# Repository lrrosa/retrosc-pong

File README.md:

# RetroSC Pong — Raspberry Pi Pico (RP2040)

Pong para 1 ou 2 jogadores em um Raspberry Pi Pico, com saída de **vídeo
composto** (NTSC 1-bit gerado por PIO) e **áudio PWM**. Foi feito para uma
máquina arcade do evento [**RetroSC**](https://retrosc.org/).

## Recursos

- Vídeo composto NTSC 256×192, 1-bit, ~60 Hz, gerado inteiramente em PIO + DMA
  (CPU livre para o jogo).
- 2 raquetes controladas por **potenciômetros 10 kΩ** (ADC do Pico).
- **Dois modos**, escolhidos no menu do attract: **arcade** (1 jogador contra a
  CPU) e **versus** (2 jogadores). Os dois jogam as mesmas fases.
- **11 fases** em sequência, em ordem crescente de dificuldade, cada uma até
  9 pontos, e cada ponto soma no **total geral**:
  1. **PONG CLASSICO** — o pong de sempre;
  2. **TRIPLO** — a raquete vira 3 pedaços de 8 px com vãos entre eles;
  3. **NAVE** — uma nave sobe e desce no meio da quadra atirando: **a bola
     rebate nela** e o tiro que pega uma raquete deixa ela pela metade por 5 s.
     Quem acerta a nave leva o troco: ela revida na hora, com um tiro pelo lado
     de quem rebateu a bola;
  4. **PEBOLIM** — cada jogador tem **três barras**, uma atrás da outra, todas
     no mesmo pot: a de trás (o goleiro, do tamanho da raquete inteira), a do
     meio e a da frente (a menor). As duas das pontas andam juntas e **a do
     meio anda ao contrário** — subir o pot desce a barra do meio. Com o pot no
     meio do curso as três se alinham, que é a posição mais fraca: quem quer
     duas linhas de defesa tem que sair do centro;
  5. **BARREIRA I** — 2 muros de tijolos quebráveis no meio da tela;
  6. **PINBALL** — sete obstáculos fixos no meio da quadra: um losango com um
     poste solto acima e outro abaixo;
  7. **BARREIRA II** — 3 muros, agora espaçados entre si;
  8. **COLUNA** — cinco dos mesmos obstáculos, empilhados no meio e subindo e
     descendo juntos;
  9. **MURALHA** — uma parede de tijolos atrás de cada raquete, com poucos vãos
     abertos de saída: só marca ponto quem enfia a bola num deles. Cada bola que
     passa da raquete derruba mais um tijolo e **o estrago fica até o fim da
     fase**, então a parede vai se abrindo e a fase acelerando;
  10. **REBOUND** — vôlei: as raquetes deitam no chão e andam na horizontal
      dentro da própria meia-quadra, a bola tem gravidade e o ponto sai quando
      ela toca o chão do lado adversário;
  11. **BARREIRA III** — 4 muros (2 por jogador), já divididos em blocos de
      5-4-2-4-5 fileiras com um corredor vazio entre eles: a mais dura, por
      isso fecha o jogo.

  Nas três barreiras o estrago fica até o fim da fase: quando abre um vão de
  ponta a ponta, aquela fase volta a ser um pong normal.
- **Mascote-bônus**: em quatro fases — **1 (clássico), 2 (triplo), 4 (barreira I)
  e 8 (muralha)**, as que têm o meio da quadra livre — o
  mascote da RetroSC cruza a tela na diagonal — às vezes de cima para baixo,
  às vezes de baixo para cima — com a palavra **BONUS** piscando ao lado. Ele
  passa **no máximo duas vezes por fase**, e acertá-lo com a bola dá um prêmio
  **sorteado na hora** para quem rebateu por último — o nome dele aparece por
  2 s do lado de quem levou. A CPU joga com as mesmas armas:

  | prêmio | o que faz |
  | --- | --- |
  | **BONUS +3** | 3 pontos **só no total geral** — o placar da fase não muda, e o total pisca um instante |
  | **RAQUETE MAIOR** | a sua raquete cresce 50% por 10 s |
  | **ENCOLHEU O RIVAL** | a raquete do adversário fica pela metade por 10 s |
  | **ESCUDO** | um muro de tijolos quebráveis aparece na frente do seu gol por 10 s; ele tem vãos por onde a bola ainda passa, some tijolo a tijolo e pisca no último segundo |
  | **TURBO** | por 10 s, cada bola que **você** rebate sai acelerada; ela volta ao normal sozinha depois de 1,5 s e só acelera de novo no seu próximo toque |

  Os quatro efeitos temporizados contam 10 s de **jogo** e atravessam o ponto:
  quem ganha no fim de um rali leva o resto do tempo para o seguinte.
  O mascote anda devagar de propósito — ele é alvo, não obstáculo. Quem limita
  a chance de acertá-lo é a duração do ponto, porque **todo ponto marcado o tira
  da tela**; por isso ele fica ~4,6 s em cena e é acertado em 1 de cada 4
  passagens.
- **Pausa**: apertar o SELETOR durante a partida abre *CONTINUAR* / *SAIR DO
  JOGO*. A escolha anda pelo **movimento** do pot (não pela posição dele), então
  o menu sempre abre em *CONTINUAR*; o SELETOR confirma e sair volta ao attract.
  Passados **30 s**, a opção destacada vale sozinha — a tela não fica parada
  para sempre numa máquina de evento.
  Ao voltar ao jogo, a raquete de quem mexeu no pot durante a pausa fica
  **piscando e parada** até o pot voltar ao lugar em que estava — pausar não
  serve para reposicionar a raquete e salvar uma bola perdida.
- **Attract screen** com logo da RetroSC + demo automático (AI vs AI),
  revezando com a tabela de recordes a cada 20 s, e um **menu de modo** que só
  aparece depois de apertar o botão **SELETOR**.
- **High scores persistentes** na flash do RP2040 com **iniciais de 3 letras**
  estilo arcade — o pot escolhe cada letra e o botão SELETOR confirma. O que
  entra no ranking é o **total acumulado** (no arcade, sempre o do humano —
  ou seja, quanto ele fez até a fase em que parou).
- Áudio com os sons clássicos do Pong (raquete, parede, ponto) mais tijolo
  quebrado e beeps do menu, em PWM filtrado.
- Botão **SELETOR**: abre o menu, escolhe o modo e confirma as iniciais.

## Estrutura do repositório

```
pong-rp2040/
├── CMakeLists.txt
├── pico_sdk_import.cmake
├── README.md
├── LICENSE
├── docs/
│   ├── schematic.md     <-- esquemático por blocos (diagramas SVG)
│   ├── pinout.md        <-- pinagem dos 3 módulos RP2040 suportados
│   ├── bom.md           <-- lista de materiais (por referência: R1, C2, J4…)
│   ├── pecas-do-gabinete.md  <-- pots, knobs e itens da caixa: qual comprar
│   └── images/          <-- diagramas, renders da placa, capturas
├── kicad/               <-- PCB: 2 variantes, gerbers prontos p/ fábrica
│   ├── README.md        <-- pipeline (esquemático -> placa -> gerbers)
│   ├── retrosc-pong*.kicad_{sch,pcb,pro}
│   ├── retrosc-pong.pretty/   <-- footprints próprios (RCA, PAM8403)
│   └── gerbers*/ + *-gerbers.zip
├── src/
│   ├── main.c
│   ├── config.h         <-- constantes do projeto (pinos, dimensões, etc.)
│   ├── ntsc.{c,h,pio}   <-- driver de vídeo composto
│   ├── gfx.{c,h}        <-- desenho no framebuffer
│   ├── font.{c,h}       <-- fonte 5x7
│   ├── input.{c,h}      <-- ADC dos pots + botão
│   ├── audio.{c,h}      <-- PWM de áudio
│   ├── highscores.{c,h} <-- persistência na flash
│   ├── game.{c,h}       <-- máquina de estados, modos e física
│   ├── phases.{c,h}     <-- as 4 fases (raquetes especiais, tijolos)
│   └── assets.{c,h}     <-- bitmaps embutidos
└── tools/
    ├── png_to_c.py      <-- conversor PNG → C array
    ├── sim.py           <-- simulador do jogo (pygame)
    ├── crt_preview.py   <-- efeito de tubo nas capturas
    ├── gen_kicad_sch.py <-- gera o esquemático  (--yd p/ a variante)
    ├── gen_kicad_fp.py  <-- gera os footprints próprios
    ├── gen_kicad_pcb.py <-- gera a placa (placement, zonas, silk, logo)
    ├── make_decoy.py    <-- placa-isca p/ o Freerouting + DSN
    ├── import_ses.py    <-- traz o roteamento de volta
    └── dsn_tweak.py     <-- ajusta larguras/isolamento no DSN
```

## Hardware

Veja os arquivos em [docs/](docs/) para detalhes:

- [docs/schematic.md](docs/schematic.md) — esquemático completo
- [docs/pinout.md](docs/pinout.md) — pinagem dos **3 módulos RP2040
  suportados** (Pico oficial, YD-RP2040 de 3 botões e "roxa" de 1 botão) e
  qual variante de PCB usar com cada um
- [docs/bom.md](docs/bom.md) — lista de materiais e custo
- [docs/pecas-do-gabinete.md](docs/pecas-do-gabinete.md) — potenciômetros,
  manoplas e peças da caixa: **qual modelo comprar** e por quê
- [kicad/README.md](kicad/README.md) — as **duas variantes de PCB** prontas
  para fabricar (gerbers zipados)

Resumo do hardware:

| Bloco | GPIO | Componentes (referências do BOM) |
| ----- | ---- | -------------------------------- |
| Vídeo composto | GP16 (sync), GP17 (video) | R1 470 Ω + R2 270 Ω → jack J1 |
| Áudio | GP18 (PWM) | filtro R3 + C1, acoplamento C2, divisor R4/R5, entradas R6/R7 → amp U2 → jacks J8/J9 |
| Botão SELETOR | GP22 | SW1 (para GND) via header J7 + filtro R9/R8/C5 na placa |
| Potenciômetro P1 | GP26 (ADC0) | RV1 10 kΩ linear + C3 → header J5 |
| Potenciômetro P2 | GP27 (ADC1) | RV2 10 kΩ linear + C4 → header J6 |

Os GPIOs acima são os mesmos nos três módulos suportados; o que muda entre
eles é **em qual furo** cada GPIO aparece (ver [pinout.md](docs/pinout.md)).

## Como compilar

### 1. Instalar o Pico SDK

**Recomendado (Windows):** baixe o [Raspberry Pi Pico Windows Installer](https://github.com/raspberrypi/pico-setup-windows/releases),
que instala toolchain (ARM GCC), CMake, Ninja, Python e o Pico SDK de uma
vez.

**Manual (qualquer SO):**

```bash
git clone --depth 1 https://github.com/raspberrypi/pico-sdk.git
cd pico-sdk
git submodule update --init
export PICO_SDK_PATH=$(pwd)
```

Instale também:

- ARM GCC (`gcc-arm-none-eabi`)
- CMake ≥ 3.13
- Ninja ou Make

### 2. Build

```bash
git clone https://github.com/lrrosa/retrosc-pong.git
cd retrosc-pong
mkdir build && cd build
cmake -G "Ninja" ..   # ou simplesmente: cmake ..
ninja                 # ou: make -j
```

Resultado: `build/pong-rp2040.uf2`.

### 3. Gravar no Pico

1. Segure o botão **BOOTSEL** do Pico enquanto conecta o USB.
2. O Pico aparece como pendrive (`RPI-RP2`).
3. Arraste `pong-rp2040.uf2` para dentro do pendrive.
4. O Pico reinicia automaticamente rodando o jogo.

## Simulador (Python, sem hardware)

Para iterar em layouts e gameplay sem flashear o Pico, há um simulador que
roda a mesma lógica em Python e carrega os MESMOS bitmaps/fonte do código C:

```bash
pip install pygame
python tools/sim.py
```

Janela 768×576 (framebuffer 256×192 × 3). Controles:

- **Mouse Y na metade esquerda** → pot P1
- **Mouse Y na metade direita** → pot P2
- **Espaço** → botão SELETOR
- **N** → pula para a próxima fase (atalho de debug)
- `--fase N` na linha de comando → começa direto na fase N (0 a 9)
- **R** → zera high scores (só em RAM, não toca a flash do Pico)
- **Q** ou **ESC** → sair

Para regerar as capturas de tela usadas aqui (roda sem abrir janela):

```bash
python tools/sim.py --shots docs/images
python tools/crt_preview.py --all
```

Pré-visualizações com efeito CRT (como deve ficar numa TV de tubo —
scanlines, glow de fósforo, vignette e curvatura):

| Attract | Menu (só após o SELETOR) | Pausa |
| :---: | :---: | :---: |
|  |  |  |

As onze fases:

| 1 · pong clássico (com o mascote-bônus) | 2 · triplo | 3 · nave |
| :---: | :---: | :---: |
|  |  |  |

| 4 · pebolim | 5 · barreira I | 6 · pinball |
| :---: | :---: | :---: |
|  |  |  |

| 7 · barreira II | 8 · coluna | 9 · muralha |
| :---: | :---: | :---: |
|  |  |  |

| 10 · rebound (vôlei) | 11 · barreira III | Fim de fase |
| :---: | :---: | :---: |
|  |  |  |

| Início de fase | Game Over | Enter Initials |
| :---: | :---: | :---: |
|  |  |  |

| High Scores | | |
| :---: | :---: | :---: |
|  | | |

Renderizações "raw" (sem CRT, só o framebuffer escalado) ficam em
`docs/images/sim_*.png`.

> **Limitação:** o simulador não reproduz a fidelidade do sinal NTSC nem
> o timing exato do PIO/DMA. Use para validar UX e visual; o teste final
> do vídeo só com a TV real.

### CRT preview

Para aplicar o efeito CRT (scanlines + bloom + fósforo + vignette +
curvatura) em qualquer PNG do framebuffer:

```bash
pip install pillow numpy
python tools/crt_preview.py docs/images/sim_attract.png        # gera crt_sim_attract.png
python tools/crt_preview.py --all                              # regenera todos os crt_*.png
```

Os parâmetros (intensidade do bloom, dos scanlines, cor do fósforo) estão
no topo de `crt_effect()` em [tools/crt_preview.py](tools/crt_preview.py)
e são bons pontos de partida; mexa neles pra ajustar pra TV verde, âmbar,
ou ajustar o "estado" do tubo.

## Simulador Wokwi (TV de verdade no navegador)

Diferente do simulador Python (que reproduz a lógica do jogo), o **Wokwi roda
o firmware compilado de verdade** no RP2040 emulado e mostra a saída de vídeo
composto numa **TV virtual** (`wokwi-tv`), com potenciômetros, botão e buzzer.

O `wokwi-tv` não usa DAC resistivo: ele lê os 2 pinos digitais direto e segue
os pulsos de sync (funciona com NTSC e PAL). Os arquivos já estão no repo:

- [`diagram.json`](diagram.json) — fiação: `GP16→SYNC`, `GP17→IN`, 2
  potenciômetros em `GP26`/`GP27`, botão SELETOR em `GP22`, buzzer em `GP18`.
- [`wokwi.toml`](wokwi.toml) — aponta para `build/pong-rp2040.uf2`/`.elf`.

Como rodar (extensão do VS Code, mais confiável que o site):

```bash
# 1. Compile o firmware
mkdir build && cd build && cmake -G Ninja .. && ninja && cd ..
# 2. No VS Code: instale a extensão "Wokwi for VS Code" e faça login (grátis)
# 3. Abra diagram.json e rode o comando "Wokwi: Start Simulator"
```

Controles no Wokwi: gire os **potenciômetros** (mouse) para mover as raquetes;
**botão verde** = SELETOR.

> **Importante:** abra a pasta `pong-rp2040` como raiz do workspace do VS Code
> (o `wokwi.toml` precisa estar na raiz). Se clicar em "play" e nada acontecer,
> rode antes `Ctrl+Shift+P` → "Wokwi: Request a New License" (token gratuito).

> **Velocidade:** o Wokwi roda a ~30% do tempo real — é normal. Emular o vídeo
> composto ciclo-a-ciclo no navegador é pesado. O **hardware real roda a 60 fps**
> (PIO + DMA fazem o vídeo, a CPU fica livre).

> **Se o Wokwi não abre no seu navegador:** ele exige WebAssembly + isolamento
> cross-origin (`SharedArrayBuffer`); extensões ou políticas às vezes bloqueiam.
> Use a **extensão do VS Code** (roda local) ou teste numa aba anônima. Se nem
> os projetos públicos do Wokwi rodam aí, conserte isso antes — não é do nosso
> projeto.

> **Centralização Wokwi × TV real:** a "janela visível" do `wokwi-tv` é
> deslocada para cima, então `LINES_TOP_BLANK` (em `src/config.h`) está em **55**
> para centralizar no simulador. Numa **TV CRT real** o centro padrão fica em
> **~30–35** — reduza esse valor (ou use o controle de V-Position/V-Hold da TV).
> A posição horizontal sai do "back porch" em `src/ntsc.pio`.

## Como jogar

- **Liga**: conecte alimentação (USB ou fonte 5 V). Sem ninguém jogando, a
  tela reveza entre o attract e a tabela de recordes.
- **Sair do attract**: aperte o **SELETOR** (vale também na tela de recordes).
  Só então o menu aparece — no attract ele fica escondido, para a tela seguir
  sendo a vitrine do jogo.
- **Escolher o modo**: com o menu aberto, **gire qualquer um dos dois pots**
  para trocar entre *MODO ARCADE* (1 jogador × CPU) e *MODO VERSUS*
  (2 jogadores) e aperte o **SELETOR** para confirmar. Sem toque nenhum por
  15 s, volta ao attract.
- **Jogar**: rode os potenciômetros para mover as raquetes (esquerda = P1,
  direita = P2 ou CPU). São **11 fases em sequência**, cada uma até **9
  pontos**, e todo ponto também soma no **total geral**. Cada fase começa com
  a bola indo para o lado de quem perdeu a fase anterior.
- **Como a partida acaba**:
  - No **modo arcade** ela termina assim que a CPU fecha uma fase — enquanto
    o jogador vencer, ele avança para a próxima. O placar dele é o total do
    que fez até ali, e a tela final mostra até que fase chegou. **A CPU melhora
    a cada fase**: a raquete dela fica mais rápida e, sobretudo, a mira vai
    ficando mais certeira — na primeira fase ela erra de propósito quase
    metade das bolas, na última quase não sobra folga.
  - No **modo versus** jogam-se as 11 fases e ganha quem tiver o maior total —
    mas a partida encerra antes se um dos dois **não alcançar mais o outro nem
    ganhando tudo o que falta**. A conta usa os pontos ainda em disputa (9 por
    fase restante, mais 6 nas fases que têm o bônus); se a diferença for
    exatamente igual a isso a partida continua, porque ainda dá empate. A tela
    de fim de fase avisa com *VANTAGEM DECISIVA*.
- **Ritmo**: a contagem 3-2-1 aparece só no primeiro ponto de cada fase; entre
  os pontos seguintes é só um "GO" rápido. Apertar o SELETOR pula as telas de
  início e de fim de fase — e, **durante a partida**, abre a pausa.
- **Iniciais**: se o total entrar no top 9, o jogador insere 3 letras estilo
  arcade — girar o pot rola pelo alfabeto A–Z, apertar o SELETOR confirma a
  letra atual e passa para a próxima. A rolagem tem **freio**: no máximo 10
  letras por segundo, e a letra em foco só troca quando o pot sai da faixa dela
  com folga, para tremor de mão não mudar nada. A tela tem **60 s**: no fim da contagem
  vale o que já estiver digitado. No modo arcade quem entra no ranking é
  sempre o humano (P1), tenha vencido ou não.
- **High scores**: depois das iniciais (ou direto, se não entrou no top),
  a tabela aparece por 10 s antes de voltar ao attract.

## Customização

Tudo importante está em [`src/config.h`](src/config.h):

- `PHASE_WIN_SCORE` — pontos para vencer **uma fase** (padrão 9). É o botão
  de volume da duração da partida. Medido no simulador: um jogador que vence
  as 11 fases leva ~19 min no arcade (quem perde na terceira sai em ~5 min), e
  uma partida versus equilibrada, que vai até a última fase, passa de 30 min —
  quando um dos dois abre vantagem decisiva ela acaba antes. Para uma fila de
  evento, **5 pontos por fase** corta isso quase pela metade sem mudar mais
  nada.
- Sons (`audio.c`) — rebatida 480 Hz, parede 640 Hz, tijolo 880 Hz e ponto
  150 Hz. Os três primeiros são **curtos** (17 a 67 ms) de propósito, e é aí que
  está a pegadinha: **alto-falante muito pequeno não toca beep curto**. Numa TV
  de 10" as rebatidas simplesmente não saem, embora o ponto (300 ms) saia; numa
  TV comum ou no amplificador do gabinete, todos aparecem. Se for testar o som,
  use um alto-falante de verdade antes de mexer nas notas.
- `AI_SPEED_MIN/MAX`, `AI_ERROR_MAX_PX/MIN_PX` — dificuldade da CPU no modo
  arcade, interpolada em linha reta entre a primeira fase e a última. Quem manda
  é o **erro de mira** (sorteado a cada rebatida): abaixo de meia raquete —
  `PADDLE_H/2`, 12 px — a bola cai sempre em cima dela e a CPU passa a não errar
  mais nada, então `AI_ERROR_MIN_PX` para em 15. A velocidade quase não muda o
  resultado: medindo no simulador, a raquete da CPU chega a ~1 px de onde mirou.
- `BALL_SPEED_*` — física da bola
- `PADDLE_W`, `PADDLE_H`, `BALL_SIZE` — visual
- `BRICK_W`, `BRICK_H`, `TRIPLE_SEG_H`, `TRIPLE_GAP` — geometria das fases
- `BONUS_*` — o mascote-bônus: velocidade, inclinação, faixa horizontal, o
  intervalo sorteado entre passagens (`BONUS_WAIT_MIN/RANGE`), quantas vezes
  ele passa por fase (`BONUS_PASSES_MAX`), quanto vale o prêmio de pontos
  (`BONUS_POINTS`) e quanto duram os outros quatro (`BONUS_EFEITO_FRAMES`)
- `PADDLE_H_BIG`, `TRIPLE_SEG_H_BIG`, `ESCUDO_PERIODO/CHEIO`, `TURBO_*` — o
  tamanho da raquete aumentada, o desenho do escudo e o pique do turbo.
  `TURBO_MAX_Q` **não é ajuste de gosto**: acima de 6 px/frame a bola atravessa
  a raquete de 3 px sem tocar nela, porque a colisão é por sobreposição
- `NAVE_*`, `SHOT_*`, `SHRINK_FRAMES` — a nave da fase 3, seus tiros e quanto
  tempo a raquete atingida fica pela metade
- `INITIALS_TIMEOUT_S`, `PAUSE_TIMEOUT_S` — o tempo que cada tela de espera
  aguarda antes de decidir sozinha: 60 s para digitar as iniciais (girar o pot
  até as 3 letras leva tempo) e 30 s na pausa
- `PWM_TOP` — resolução do PWM de áudio. É ela que fixa a **nota mais grave**
  possível, em `sysclk / (255 · (PWM_TOP+1))`; abaixo disso o som sai na nota
  errada, porque o divisor do PWM satura
- `BUMPER_*`, `COL_*`, `BUMPER_SPIN_SHIFT` — os obstáculos do pinball e da
  coluna móvel, e o quanto cada rebote neles gira a bola (o que impede que ela
  entre em vaivém eterno entre dois postes)
- `PAUSE_POT_STEP`, `PADDLE_TAKEOVER_TOL` — quanto girar o pot para trocar o
  item da pausa e a folga para a raquete voltar a obedecer depois dela
- `GRAVITY_Q`, `VOLLEY_*`, `NET_TOP` — a física do Rebound (vôlei)
- `MENU_TIMEOUT_S` — tempo até o menu desistir e voltar ao attract
- Pinos GPIO

As fases em si estão em [`src/phases.c`](src/phases.c): o enum `phase_id_t`,
as tabelas de nome/dica e as funções `build_*()`. Uma fase pode mexer em
quatro coisas — o formato/orientação da raquete, os tijolos e sólidos da
quadra, o ponto de saque e as *flags* (`PF_GRAVITY`, `PF_FLOOR_SCORES`,
`PF_SIDE_WALLS`, `PF_PADDLE_HORIZ`, `PF_NO_CENTER_LINE`, `PF_TEM_BONUS`) que
dizem ao `game.c` como tratar as bordas e a física e se o mascote-bônus
aparece ali. Para acrescentar uma fase basta um
item no enum, um nome/dica nas tabelas e o que ela tem de especial — o resto
do jogo (pontuação, menu, telas) não muda.

Ideias ainda na fila estão anotadas no topo de `phases.c`.

Para trocar o logo do attract:

```bash
python tools/png_to_c.py docs/images/seu_logo.png retrosc_logo 0 0 threshold > tools/_logo.inc
# Substituir o array correspondente em src/assets.c
```

Modo `threshold` (corte fixo em 128) é melhor para arte com contornos
definidos (logos, ícones). Modo `dither` (Floyd-Steinberg) é melhor para
fotos com gradientes — mas em 60 Hz num CRT, o padrão de dithering pode
ficar tremido. Para o evento, prefira `threshold`.

Veja `docs/images/preview_logo_1bit.png` para saber como ficou a versão
1-bit.

## Testes de regressão

Com Python 3 e um GCC ou Clang **nativo do computador** (não o compilador ARM):

```bash
python tools/check_firmware.py
python tools/check_firmware.py --cc /caminho/para/gcc --sanitize
python tools/check_docs.py
```

No Windows, `--cc C:\msys64\ucrt64\bin\gcc.exe` seleciona o GCC do MSYS2.
Os executáveis de teste ficam em `build/tests/`. A opção `--sanitize` faz o
programa falhar ao detectar comportamento indefinido em C.

Os testes executam o **código C real** com ADC, GPIO, áudio e flash simulados:
colisões com turbo, conservação de velocidade, curso dos potenciômetros,
debounce, menu, pausa, timeouts, recordes e saques das 11 fases. Também executam
330 mil frames e comparam 2.200 cenários de física com o simulador Python,
sem exigir Pygame. O teste de flash verifica o formato e o checksum em memória;
PIO, DMA, sinais elétricos e gravação física continuam exigindo teste na placa.

## Limitações conhecidas

- **NTSC monocromático**: sem cor. Em TVs PAL-M brasileiras, a maioria
  aceita o sinal sem problema (mostra em preto e branco). Se sua TV não
  aceita, talvez precise de uma TV CRT com entrada AV "real" ou um
  conversor.
- **Timing do PIO** está calculado para `clk_sys = 125 MHz`. Se você
  alterar o clock, ajuste `clkdiv` em `src/ntsc.c` proporcionalmente.
- **Serigrafia da PCB**: as placas da v1 têm o botão serigrafado como
  **START** (a net no KiCad também se chama `START`). O firmware, os diagramas
  e as telas já o chamam de **SELETOR** — é o mesmo botão no GP22.
- **Tabela de high scores zera ao atualizar**: ela passou a ter 9 entradas em
  vez de 5, o que muda o tamanho do registro gravado (`HISCORE_VERSION 4`),
  então a tabela gravada por firmwares antigos é descartada na primeira
  execução.

## Créditos e referências

- A abordagem de gerar NTSC com duas PIOs (sync + dados) + DMA é inspirada
  no trabalho de [@brucland](https://github.com/brucland/RP2040/tree/main/PIO/NTSC_1_bit).
  Este projeto é uma implementação independente (não copia o código), mas a
  análise daquele repositório foi essencial para definir o timing.
- Pong original: Allan Alcorn, Atari (1972).
- Logo da RetroSC: cortesia do evento [RetroSC](https://retrosc.org/).

## Licença

Projeto com **licença dupla** (ver [`NOTICE`](NOTICE) para o detalhamento por
arquivo):

- **Software** (firmware em `src/`, ferramentas em `tools/`, build) —
  **[GPL-3.0-or-later](LICENSE)** (`SPDX-License-Identifier: GPL-3.0-or-later`).
- **Hardware** (esquemáticos: `kicad/`, `docs/schematic.md`, `docs/bom.md`,
  `docs/pinout.md`, diagramas SVG) — **[CERN-OHL-S-2.0](LICENSE-HARDWARE.txt)**
  (`SPDX-License-Identifier: CERN-OHL-S-2.0`), a variante *Strongly Reciprocal*
  da CERN Open Hardware Licence.

As duas são **recíprocas** (copyleft): trabalhos derivados devem manter a mesma
licença e disponibilizar as fontes correspondentes (código no caso do software,
arquivos de projeto no caso do hardware).

As **marcas e arte do evento RetroSC** (logo) permanecem propriedade do evento e
**não** estão cobertas por essas licenças — ver [`NOTICE`](NOTICE).

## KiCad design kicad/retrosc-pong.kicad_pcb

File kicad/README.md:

# PCB — RetroSC Pong

Placa de 2 camadas com plano de terra, gerada por scripts (reprodutível) e
roteada com o Freerouting. Hardware sob **CERN-OHL-S-2.0** (ver
[`../LICENSE-HARDWARE.txt`](../LICENSE-HARDWARE.txt)).

| Montada | Sem componentes (serigrafia à mostra) |
| :---: | :---: |
|  |  |

**80 × 66 mm**, imagens da variante oficial (a YD é idêntica por fora; muda só
o roteamento). O logo RetroSC fica **embaixo do Pico** — por isso aparece na
serigrafia e não no render 3D. Layout detalhado em [Estado](#estado).

> O **Pico é o único componente com modelo 3D** (os footprints próprios do RCA
> e do PAM8403 não têm) — e é justamente ele que cobre o logo. Por isso a
> segunda vista é renderizada **sem componentes**: é nela que se confere a
> serigrafia. As três saem do passo 8 do pipeline.

**Duas variantes**, escolhidas pelo módulo RP2040 que você tem (mesma
furação, pinagens diferentes — ver [../docs/pinout.md](../docs/pinout.md) e
as marcas GP17/GP18 no silk):

| Variante | Módulo | Arquivos |
| --- | --- | --- |
| oficial | Raspberry Pi Pico **ou** YD-RP2040 de **3 botões** (pinagem ≈ Pico) | `retrosc-pong.*`, `gerbers/`, `retrosc-pong-gerbers.zip` |
| YD | RP2040 **roxa de 1 botão** (USB-C, 16 MB) | `retrosc-pong-yd.*`, `gerbers-yd/`, `retrosc-pong-yd-gerbers.zip` |

> Atenção: existem clones parecidos com pinagens diferentes entre si. O que
> define a variante é a **pinagem**, não a cor/marca — na dúvida, confira a
> tabela completa em `docs/pinout.md` e as marcas GP17/GP18.

## Como fabricar (é só isto)

1. Escolha a variante pela tabela acima — **qual módulo RP2040 você tem**.
2. Baixe o ZIP correspondente (`retrosc-pong-gerbers.zip` ou
   `retrosc-pong-yd-gerbers.zip`) e envie **como está** para a fábrica
   (JLCPCB, PCBWay, Elecrow…).
3. Parâmetros: **2 camadas, 1,6 mm, HASL**, 80 × 66 mm. Os defaults de
   qualquer fábrica servem — não há nada exótico na placa.
4. Peças e montagem: [../docs/bom.md](../docs/bom.md).

Não é preciso instalar KiCad nem rodar nada. O pipeline abaixo só interessa
para **modificar** o projeto.

## Arquivos versionados

| Arquivo | O quê |
| --- | --- |
| `retrosc-pong[-yd].kicad_sch` / `.kicad_pro` | esquemático e projeto |
| `retrosc-pong[-yd].kicad_pcb` | **placa roteada** (DRC 0 erros) |
| `retrosc-pong.pretty/` | footprints próprios (RCA de painel, PAM8403 HW-012) |
| `fp-lib-table` | registra a lib de footprints do projeto |
| `gerbers[-yd]/` | Gerbers + furação (Excellon) prontos para fábrica |
| `retrosc-pong[-yd]-gerbers.zip` | os mesmos gerbers zipados — **baixe e envie direto à fábrica** |
| `../docs/retrosc-pong[-yd]-esquematico.pdf` | esquemático completo em 1 folha (para montar/conferir) |

Intermediários (`*-decoy.*`, `*.dsn`, `*.ses`, `*.net`) são **gitignored** —
regeráveis pelo pipeline abaixo.

## Pipeline (do zero à placa roteada) — só para modificar

Esta seção é para quem vai **alterar** a placa: tudo é gerado por script, então
não se edita o `.kicad_pcb` à mão — muda-se o gerador e roda-se o pipeline de
novo. Requer o **Python do KiCad** (`.../KiCad/10.0/bin/python.exe`, módulo `pcbnew`),
`kicad-cli` e o **Freerouting** instalado.

```sh
KPY="/c/Program Files/KiCad/10.0/bin/python.exe"
CLI="/c/Program Files/KiCad/10.0/bin/kicad-cli.exe"
FR="$LOCALAPPDATA/freerouting/freerouting.exe"

# 1. esquemático -> netlist  (roda no Python normal)
python tools/gen_kicad_sch.py
python tools/gen_kicad_fp.py
"$CLI" sch export netlist -o kicad/retrosc-pong.net kicad/retrosc-pong.kicad_sch

# 2. placa (placement, contorno, zonas, regras)   [Python do KiCad]
"$KPY" tools/gen_kicad_pcb.py

# 3. ISCA sem zonas + DSN                          [Python do KiCad]
"$KPY" tools/make_decoy.py

# 4. roteamento automatico  (caminhos relativos: sem espacos)
"$FR" -de kicad/retrosc-pong-decoy.dsn -do kicad/retrosc-pong-decoy.ses -mp 100 -da

# 5. importar SES na placa real + remover trilhas de GND  [Python do KiCad]
"$KPY" tools/import_ses.py

# 6. preencher o plano e validar
"$CLI" pcb drc --refill-zones --save-board --severity-error \
       --exit-code-violations kicad/retrosc-pong.kicad_pcb

# 7. gerbers + furacao + zip para a fabrica
"$CLI" pcb export gerbers --layers "F.Cu,B.Cu,F.SilkS,B.SilkS,F.Mask,B.Mask,Edge.Cuts" \
       --subtract-soldermask -o kicad/gerbers/ kicad/retrosc-pong.kicad_pcb
"$CLI" pcb export drill --format excellon --drill-origin absolute \
       --excellon-units mm --generate-map --map-format gerberx2 \
       -o kicad/gerbers/ kicad/retrosc-pong.kicad_pcb
powershell -c "Compress-Archive -Path kicad\gerbers\* -DestinationPath kicad\retrosc-pong-gerbers.zip -Force"

# 8. imagens do README (montada, sem componentes, isometrica)
"$KPY" tools/render_placa.py

# 9. esquemático em PDF/SVG (o que se usa para montar e conferir)
"$CLI" sch export pdf -o docs/retrosc-pong-esquematico.pdf kicad/retrosc-pong.kicad_sch
"$CLI" sch export svg --no-background-color -o docs/images/kicad/ kicad/retrosc-pong.kicad_sch
# 10. desenho de encaixe na caixa            [Python do KiCad]
"$KPY" tools/fit_caixa.py
```

**Variante YD-RP2040:** repita os passos com `--yd` nos scripts Python e o
sufixo `-yd` nos nomes de arquivo (`retrosc-pong-yd.*`, `gerbers-yd/`). Entre
os passos 3 e 4, afine a trilha de sinal para 0,25 mm (com 0,30 mm o net
SELETOR não fecha nessa variante) e peça **0,17 mm de isolamento** ao roteador
— pedindo os 0,15 do projeto ele entrega 0,1478 e o DRC reprova:

```sh
python tools/dsn_tweak.py kicad/retrosc-pong-yd-decoy.dsn 250 500 170
```

**Por que a isca (passo 3):** com as zonas presentes, o DSN as exporta como
*planes* que o Freerouting trata como obstáculo — ele vira quase mono-camada e
abandona os nets longos. Sem zonas, roteia livre nas 2 faces; o plano de GND
volta na placa real e absorve todo o GND (passo 5 remove as trilhas de GND
redundantes).

## Estado

- **Placa 80 × 66 mm**, dimensionada para a caixa **Patola PB-085/3**
  (85 × 73 × 32 mm; interno ~82 × 70). Pico à esquerda com o USB na borda de
  cima; PAM8403 no topo à direita, corpo na placa e pot de volume saindo pela
  mesma borda; os 3 RCAs na borda direita com o **barril protraindo ~10 mm**
  (atravessa a parede da caixa); headers de painel em **uma fileira** na borda
  de baixo, cada pino com a função na serigrafia.
- **Nada de trilha sob os parafusos:** cada furo leva uma **área de exclusão
  de raio 3,6 mm** (rule area nas 2 faces) que barra trilhas e vias — sem
  ela o roteador passava sinal a 2 mm do centro, ou seja, 0,4 mm da borda do
  furo, bem debaixo da cabeça do parafuso. O plano de GND continua entrando
  (encostar em GND é inofensivo). `make_decoy.py` **preserva** essas áreas ao
  montar a isca, senão o roteador não as enxergaria.
- **Furos de montagem: 2, a 58 mm entre centros**, na linha de centro da
  largura — H1 (40, 4) e H2 (40, 62). É a furação dos **bossos da tampa** da
  PB-085/3 (2 bossos com furo-guia ø2,5, a 58 mm, no centro do lado de
  85 mm). Em troca, o miolo das bordas de cima e de baixo (x 36,5..43,5)
  fica reservado — nenhum componente pode ocupá-lo.
- **Filtro do SELETOR na placa:** R9 (220 Ω em série) e C5 (100 nF para o
  plano de terra) ficam **colados no header J7**, na faixa livre logo acima
  dele — é no conector que a descarga do painel de alumínio entra, e é ali que
  ela tem que morrer. O R8 (pull-up externo de 4,7 kΩ) é só DC e ficou com os
  passivos do áudio, à direita do R6. Por que o filtro existe:
  [../docs/schematic.md](../docs/schematic.md#botão-seletor).
- **J5 + J6 (pots)** ficam na mesma fileira com **uma posição vaga** entre
  eles: um único conector fêmea 1×7 (2,54 mm) serve os dois, deixando o
  contato do meio sem uso. Por isso o par é indivisível — e, como não cabia
  junto do J4 sem os rótulos se embaralharem, a ordem na borda de baixo é
  **J4 · J7 · (J5 J6)**: o SELETOR (serigrafado START na v1), que é independente, ficou à esquerda e o
  par dos pots à direita do furo de montagem.
- **Encaixe na caixa** (desenho em escala abaixo): folga de **1,0 mm** nas
  laterais e **2,0 mm** em cima/embaixo; os 2 furos caem exatamente sobre os
  bossos da tampa. Recortes necessários na parede: **3 RCAs à direita**
  (barril passa 8,3 mm da face externa), **pot do amp em cima** (11,6 mm) e
  **USB em cima** — este último *não* protrai: a face do conector fica 1,2 mm
  para dentro, então o recorte precisa deixar o plugue entrar.

  > O desenho sai de `tools/fit_caixa.py`, que lê a geometria da própria
  > placa — refaça-o a cada mudança de layout. **A altura** (26 mm internos)
  > não está no desenho: confira na peça real, principalmente o eixo do pot e
  > os barris dos RCAs, cuja altura depende de quanto o parafuso afasta a
  > placa dos bossos.
- **Logo RetroSC no silk da frente**, dentro do espaço do Pico (48,4 ×
  15,2 mm a 0,22 mm/pixel, entre as duas fileiras de pinos — fica visível
  antes da montagem ou com o Pico socketado). Gerado de
  `docs/images/logo_retrosc_1bit.png` com preto/branco invertidos (o traço
  do logo é a tinta). O logo é marca do evento e **não** é coberto pelas
  licenças do projeto.
- **Marcas GP17/GP18 no silk** ao lado dos furos correspondentes de cada
  variante (Pico: coluna direita, posições 22/24; YD-RP2040: cantos da base,
  posições 20/21). Antes de soldar, confira se elas batem com os rótulos do
  seu módulo — é o jeito rápido de ver se a placa e o módulo são da mesma
  variante.
- **Serigrafia:** rótulos de função por pino, nome + referência em cada
  header (ex.: `POT P1 (J5)`), marcas GP17/GP18 **com linha de chamada** até
  o pino exato, e os nomes dos RCAs **na vertical**, encostados em cada jack
  (assim acompanham a altura do conector e não invadem a faixa dos headers).
  No meio da placa fica a assinatura `RetroSC Pong v1.0` + `LRRosa 2026` — a
  segunda linha foi 4 mm para a direita quando o C5 entrou, senão o texto
  passava por cima de um pad dele. As referências que
  caíam sobre pads (J*, H*) foram ocultadas — a informação está nos rótulos
  descritivos. O logo foi reescalado (0,19 mm/px) para caber **entre** as
  duas linhas verticais do footprint do Pico.
- **DRC: 0 erros**, 0 silk sobre cobre e 0 sobreposições. Restam 12 avisos
  de `silk_edge_clearance`: são o desenho do USB e dos barris dos RCAs
  cruzando a borda — intencional, é por ali que eles saem da caixa.
- Regras: trilha de sinal 0,3 mm, isolamento 0,15 mm, via 0,7/0,35 mm (JLCPCB
  2 camadas).

## ATENÇÃO antes de fabricar

- **Footprints do RCA e do PAM8403 foram feitos à mão** a partir de medidas das
  peças. Confira o encaixe (imprima o **desenho de fabricação** em 1:1 e
  sobreponha as peças) antes de enviar para produção.
- Peças de **painel** (pots, botão, chave A/B) saem por headers (J4–J7); os RCAs
  e o amp ficam **na placa**, como no protótipo.

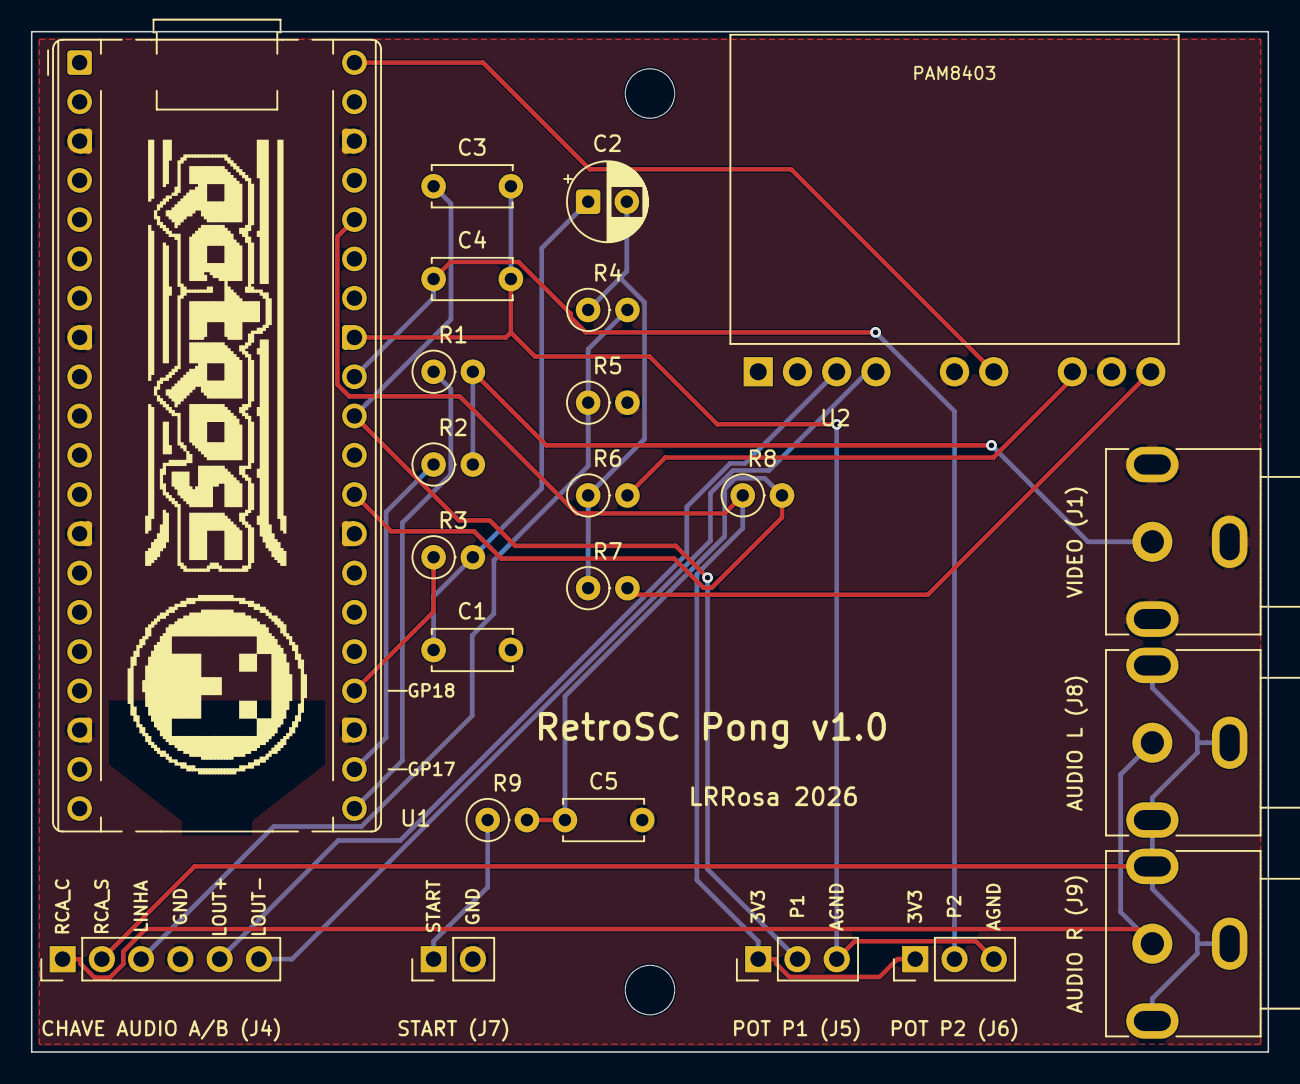
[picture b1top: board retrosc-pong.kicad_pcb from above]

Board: 2 copper layers, 80.0 x 66.0 mm, 25 parts (0 on the bottom side), 21 nets.

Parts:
C1, C3, C4, C5: 100n; C_Disc_D5.0mm_W2.5mm_P5.00mm
C2: 1u; CP_Radial_D5.0mm_P2.50mm
H1, H2: MountingHole_3.2mm_M3
J1: RCA video (na placa); RCA_Jack_THT_Panel
J4: chave A/B (painel); PinHeader_1x06_P2.54mm_Vertical
J5: pot P1 (painel); PinHeader_1x03_P2.54mm_Vertical
J6: pot P2 (painel); PinHeader_1x03_P2.54mm_Vertical
J7: START (painel); PinHeader_1x02_P2.54mm_Vertical
J8: RCA audio L (na placa); RCA_Jack_THT_Panel
J9: RCA audio R (na placa); RCA_Jack_THT_Panel
R1: 470; R_Axial_DIN0207_L6.3mm_D2.5mm_P2.54mm_Vertical
R2: 270; R_Axial_DIN0207_L6.3mm_D2.5mm_P2.54mm_Vertical
R3, R5, R6, R7: 1k; R_Axial_DIN0207_L6.3mm_D2.5mm_P2.54mm_Vertical
R4: 10k; R_Axial_DIN0207_L6.3mm_D2.5mm_P2.54mm_Vertical
R8: 4k7; R_Axial_DIN0207_L6.3mm_D2.5mm_P2.54mm_Vertical
R9: 220; R_Axial_DIN0207_L6.3mm_D2.5mm_P2.54mm_Vertical
U1: RaspberryPi_Pico; RaspberryPi_Pico_Common_THT
U2: PAM8403 HW-012; PAM8403_HW-012

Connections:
+3V3: J5.1, J6.1, R8.1, U1.36
+5V: U1.40, U2.6
AGND: C3.2, C4.2, J5.3, J6.3, U1.33
AMP_L: R6.2, U2.7
AMP_R: R7.2, U2.9
AUDIO_PWM: R3.1, U1.24
AUD_C: C2.2, R4.1, R6.1, R7.1
AUD_F: C1.1, C2.1, R3.2
COMPOSITE: J1.1, R1.2, R2.2
GND: C1.2, C5.2, J1.2, J4.4, J7.2, R5.2, U1.3, U1.8, U1.13, U1.18, U1.23, U1.28, U1.38, U2.5, U2.8
LINHA: J4.3, R4.2, R5.1
LOUT_N: J4.6, U2.4
LOUT_P: J4.5, U2.3
POT1: C3.1, J5.2, U1.31
POT2: C4.1, J6.2, U1.32
RCA_C: J4.1, J8.1, J9.1
RCA_S: J4.2, J8.2, J9.2
START: C5.1, R8.2, R9.2, U1.29
START_SW: J7.1, R9.1
SYNC: R1.1, U1.21
VIDEO: R2.1, U1.22

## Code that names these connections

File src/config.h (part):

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
// ===== Pinos =====
// Video composto: DAC resistivo de 2 bits.
//   SYNC_PIN  --[470 ohm]--+
//   VIDEO_PIN --[270 ohm]--+---- RCA center (composite out)
//                          +---- 75 ohm  ---- GND (terminacao da TV)
#define NTSC_SYNC_PIN     16
#define NTSC_VIDEO_PIN    17
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// ===== Video =====
#define FB_WIDTH          256
#define FB_HEIGHT         192
#define FB_STRIDE_WORDS   (FB_WIDTH / 32)   // 8 words por linha
#define FB_WORDS          (FB_STRIDE_WORDS * FB_HEIGHT)

#define LINES_PER_FRAME   262
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

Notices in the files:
src/config.h:
Copyright (C) 2026 Leonardo Roman da Rosa
